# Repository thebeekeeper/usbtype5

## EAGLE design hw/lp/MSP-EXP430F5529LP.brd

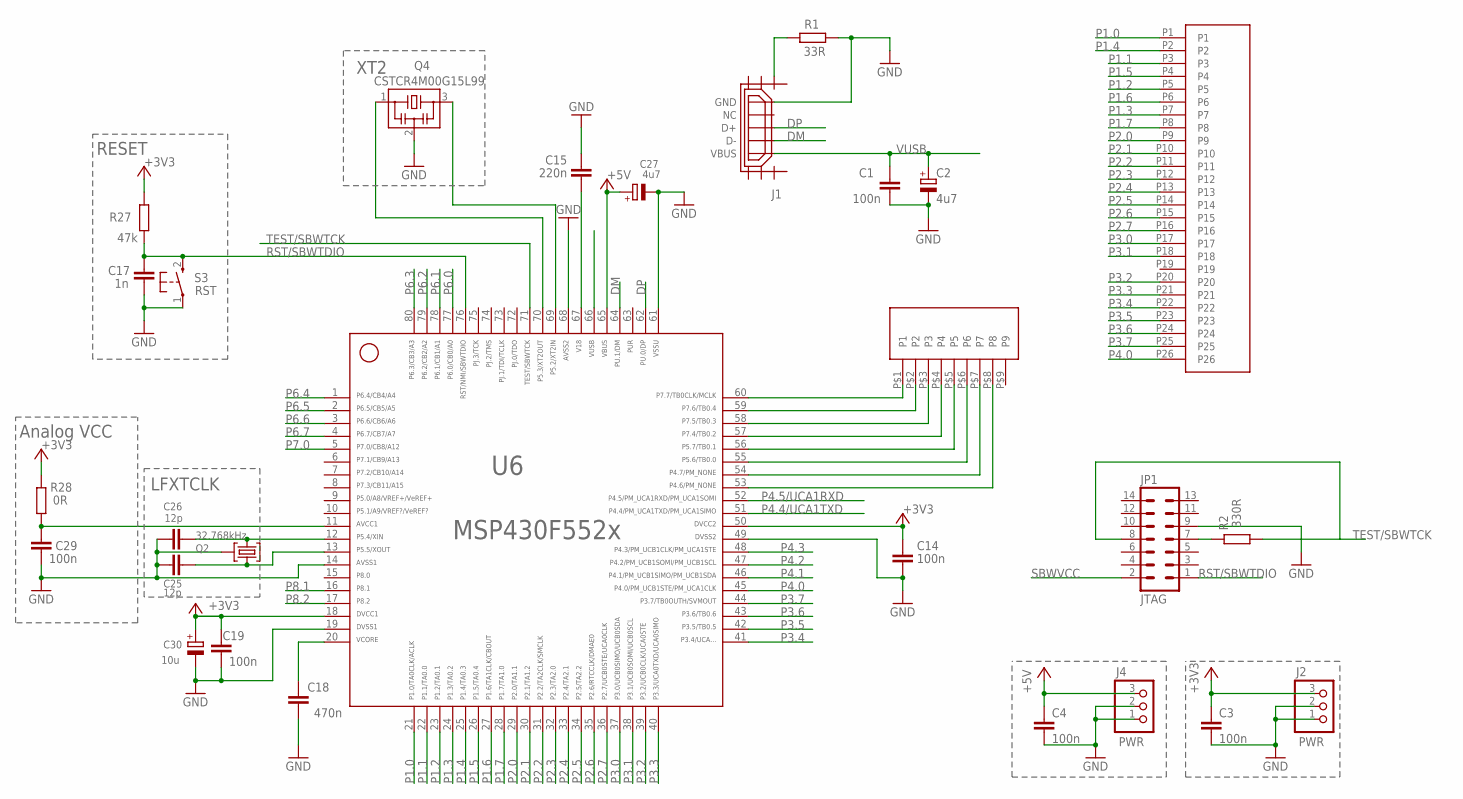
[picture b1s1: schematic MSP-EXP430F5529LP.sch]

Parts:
C1, C3, C4, C14, C19, C29: 100n; C0402
C2, C27: 4u7; A/3216-18R
C15: 220n; C0402
C17: 1n; C0402
C18: 470n; C0402
C25, C26: 12p; C0402
C30: 10u; A/3216-18R
J1: USB_MICRO_FLIPPED; HIROSE-ZX62R-B-5P
J2, J4: PWR; 1X03
JP1: JTAG; MA07-2
Q2: 32.768kHz; MS3V-T1R
Q4: CSTCR4M00G15L99; MURATA-FILTER_CSTCR
R1: 33R; R0402
R2: 330R; R0402
R27: 47k; R0402
R28: 0R; R0402
S3: RST; PBTH
U6: MSP430F5529IPNR; PN80
U$1: 52806-0910; SD-52806-09
U$2: 52808-267126; SD-52808-025

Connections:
+3V3: C3.1, C14.1, C19.2, C30.+, J2.3, R27.2, R28.2, U6.18, U6.50
+5V: C4.1, C27.+, J4.3, U6.65
AVCC: C29.1, R28.1, U6.11
DM: J1.D-, U6.64
DP: J1.D+, U6.62
GND: C1.2, C2.-, C3.2, C4.2, C14.2, C15.2, C17.2, C18.1, C19.1, C25.1, C26.1, C27.-, C29.2, C30.-, J1.GND, J2.1, J2.2, J4.1, J4.2, JP1.9, Q2.P3 (GND), Q4.2, R1.2, S3.1, U6.14, U6.19, U6.49, U6.61, U6.68
unnamed: JP1.7, R2.2
unnamed: U6.60, U$1.P$1 (P1)
unnamed: U6.59, U$1.P$2 (P2)
unnamed: U6.58, U$1.P$3 (P3)
unnamed: U6.57, U$1.P$4 (P4)
unnamed: U6.56, U$1.P$5 (P5)
unnamed: U6.55, U$1.P$6 (P6)
unnamed: U6.54, U$1.P$7 (P7)
unnamed: U6.53, U$1.P$8 (P8)
unnamed: J1.SHIELD1, R1.1
P1.0: U6.21, U$2.P1
P1.1: U6.22, U$2.P3
P1.2: U6.23, U$2.P5
P1.3: U6.24, U$2.P7
P1.4: U6.25, U$2.P2
P1.5: U6.26, U$2.P4
P1.6: U6.27, U$2.P6
P1.7: U6.28, U$2.P8
P2.0: U6.29, U$2.P9
P2.1: U6.30, U$2.P10
P2.2: U6.31, U$2.P11
P2.3: U6.32, U$2.P12
P2.4: U6.33, U$2.P13
P2.5: U6.34, U$2.P14
P2.6: U6.35, U$2.P15
P2.7: U6.36, U$2.P16
P3.0: U6.37, U$2.P17
P3.1: U6.38, U$2.P18
P3.2: U6.39, U$2.P20
P3.3: U6.40, U$2.P21
P3.4: U6.41, U$2.P22
P3.5: U6.42, U$2.P23
P3.6: U6.43, U$2.P24
P3.7: U6.44, U$2.P25
P4.0: U6.45, U$2.P26
P4.1: U6.46
P4.2: U6.47
P4.3: U6.48
P4.4/UCA1TXD: U6.51
P4.5/UCA1RXD: U6.52
P5.2/XT2IN: Q4.3, U6.69
P5.3/XT2OUT: Q4.1, U6.70
P5.4/XIN: C26.2, Q2.P2 (2), U6.12
P5.5/XOUT: C25.2, Q2.P1 (1), U6.13
P6.0: U6.77
P6.1: U6.78
P6.2: U6.79
P6.3: U6.80
P6.4: U6.1
P6.5: U6.2
P6.6: U6.3
P6.7: U6.4
P7.0: U6.5
P8.1: U6.16
P8.2: U6.17
RST/SBWTDIO: C17.1, JP1.1, R27.1, S3.2 (S), U6.76
SBWVCC: JP1.2
TEST/SBWTCK: JP1.8, R2.1, U6.71
V18: C15.1, U6.67
VCORE: C18.2, U6.20
VUSB: C1.1, C2.+, J1.VBUS, U6.66

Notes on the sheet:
RESET
LFXTCLK
XT2
Analog VCC

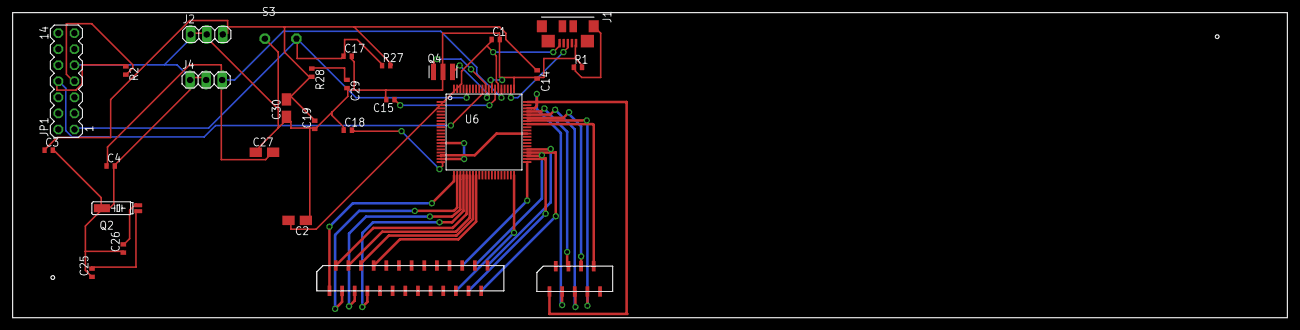
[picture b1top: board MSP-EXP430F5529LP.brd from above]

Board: 2 copper layers, 201.5 x 48.1 mm, 28 parts (0 on the bottom side), 50 nets.

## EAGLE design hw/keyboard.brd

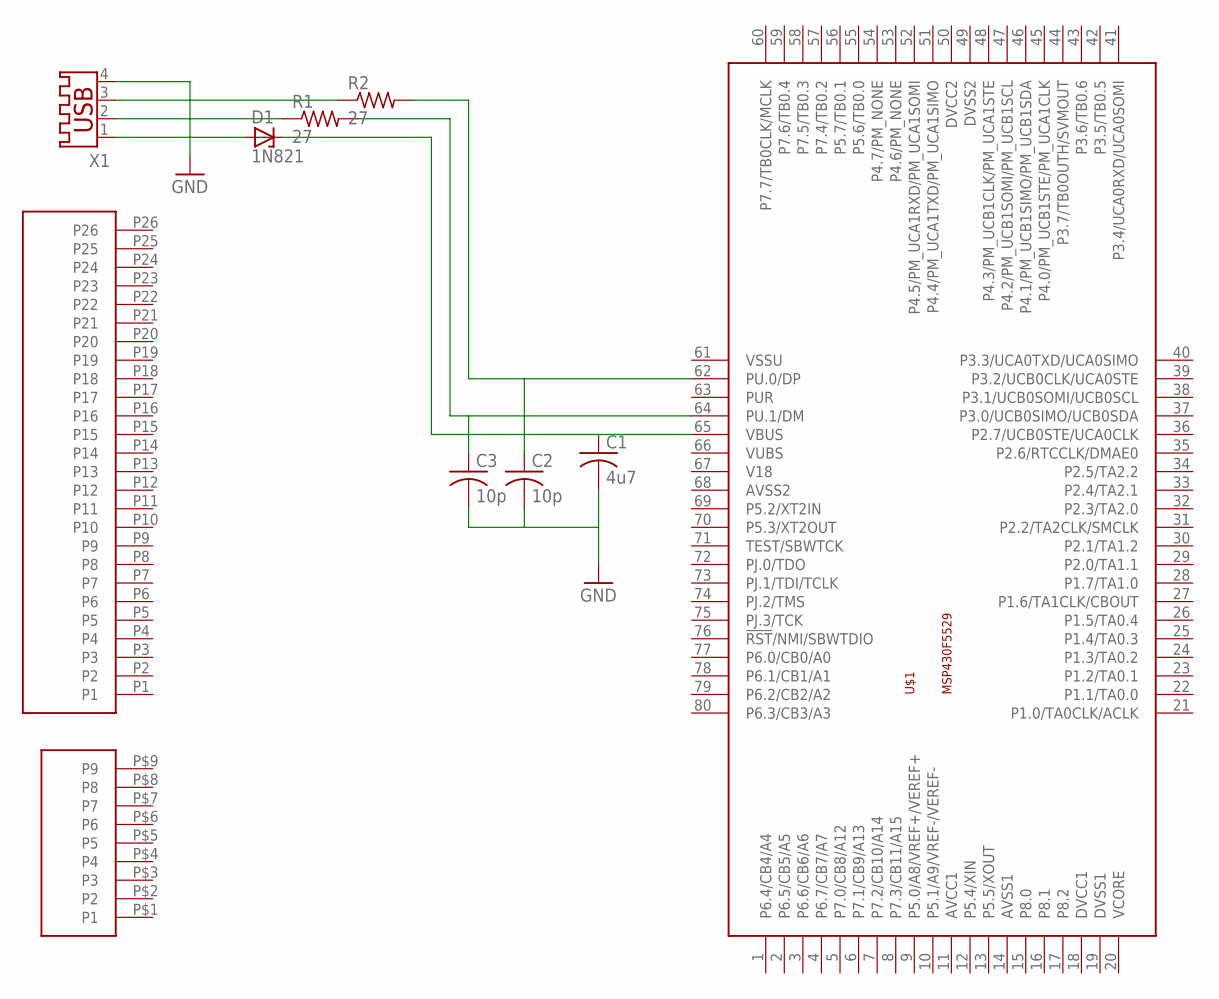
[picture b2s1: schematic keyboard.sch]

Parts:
C1: 4u7; C0805
C2, C3: 10p; C0805
D1: 1N821; DO35Z10
R1, R2: 27; R0603
U$1: MSP430F5529; PN_S-PQFP-G80
U$2: 52808-267126; SD-52808-025
U$3: 52806-0910; SD-52806-09
X1: USB-A003

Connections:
GND: C1.2, C2.2, C3.2, X1.4
unnamed: C3.1, R1.2, U$1.64 (PU.1/DM)
unnamed: C2.1, R2.2, U$1.62 (PU.0/DP)
unnamed: D1.A, X1.1
unnamed: C1.1, D1.C, U$1.65 (VBUS)
unnamed: R1.1, X1.2
unnamed: R2.1, X1.3

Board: 2 copper layers, 10 parts (0 on the bottom side), 7 nets, no tracks yet.

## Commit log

2014-01-19 adding schematics
2014-01-20 software spike based off of app note
2014-01-20 adding usb power need ldos
2014-01-20 figuring out a pattern for matrix scanning
